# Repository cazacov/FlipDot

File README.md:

# Flip-Dot Displays

Repository structure
## Hardware
Information about flip-dot matrices and controllers.
### Lawo-34 pins
Flip-dot matrices with 34-pins connector having 3 driver chips. For example produced by Lawo.

### Brose-60 pins
Flip-dot matrices with 60-pins connector having 1 driver chip. For example produced by Brose.

### RS-422 Brose VM_IIC

Matrix controller with RS-422 interface

---
All trademarks, logos and brand names are the property of their respective owners. All company, product and service names are for identification purposes only. 

It's a hobby project; I am not affiliated with any  company producing flip-dot displays.

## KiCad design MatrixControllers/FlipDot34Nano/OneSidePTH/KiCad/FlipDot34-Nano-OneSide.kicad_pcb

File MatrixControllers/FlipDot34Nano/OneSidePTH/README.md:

### FlipDot34Nano - One Side PTH

Driver board with Arduino Nano and three 74HC595 shift registers opitmized for single-sided PCB that can be milled with 3018 CNC. 3 digital pins are used for controlling shift registers, analog pins A4 and A5 can be used to receive commands over I2C. Pins A0-A2 connected to DIP switches choosing I2C address.

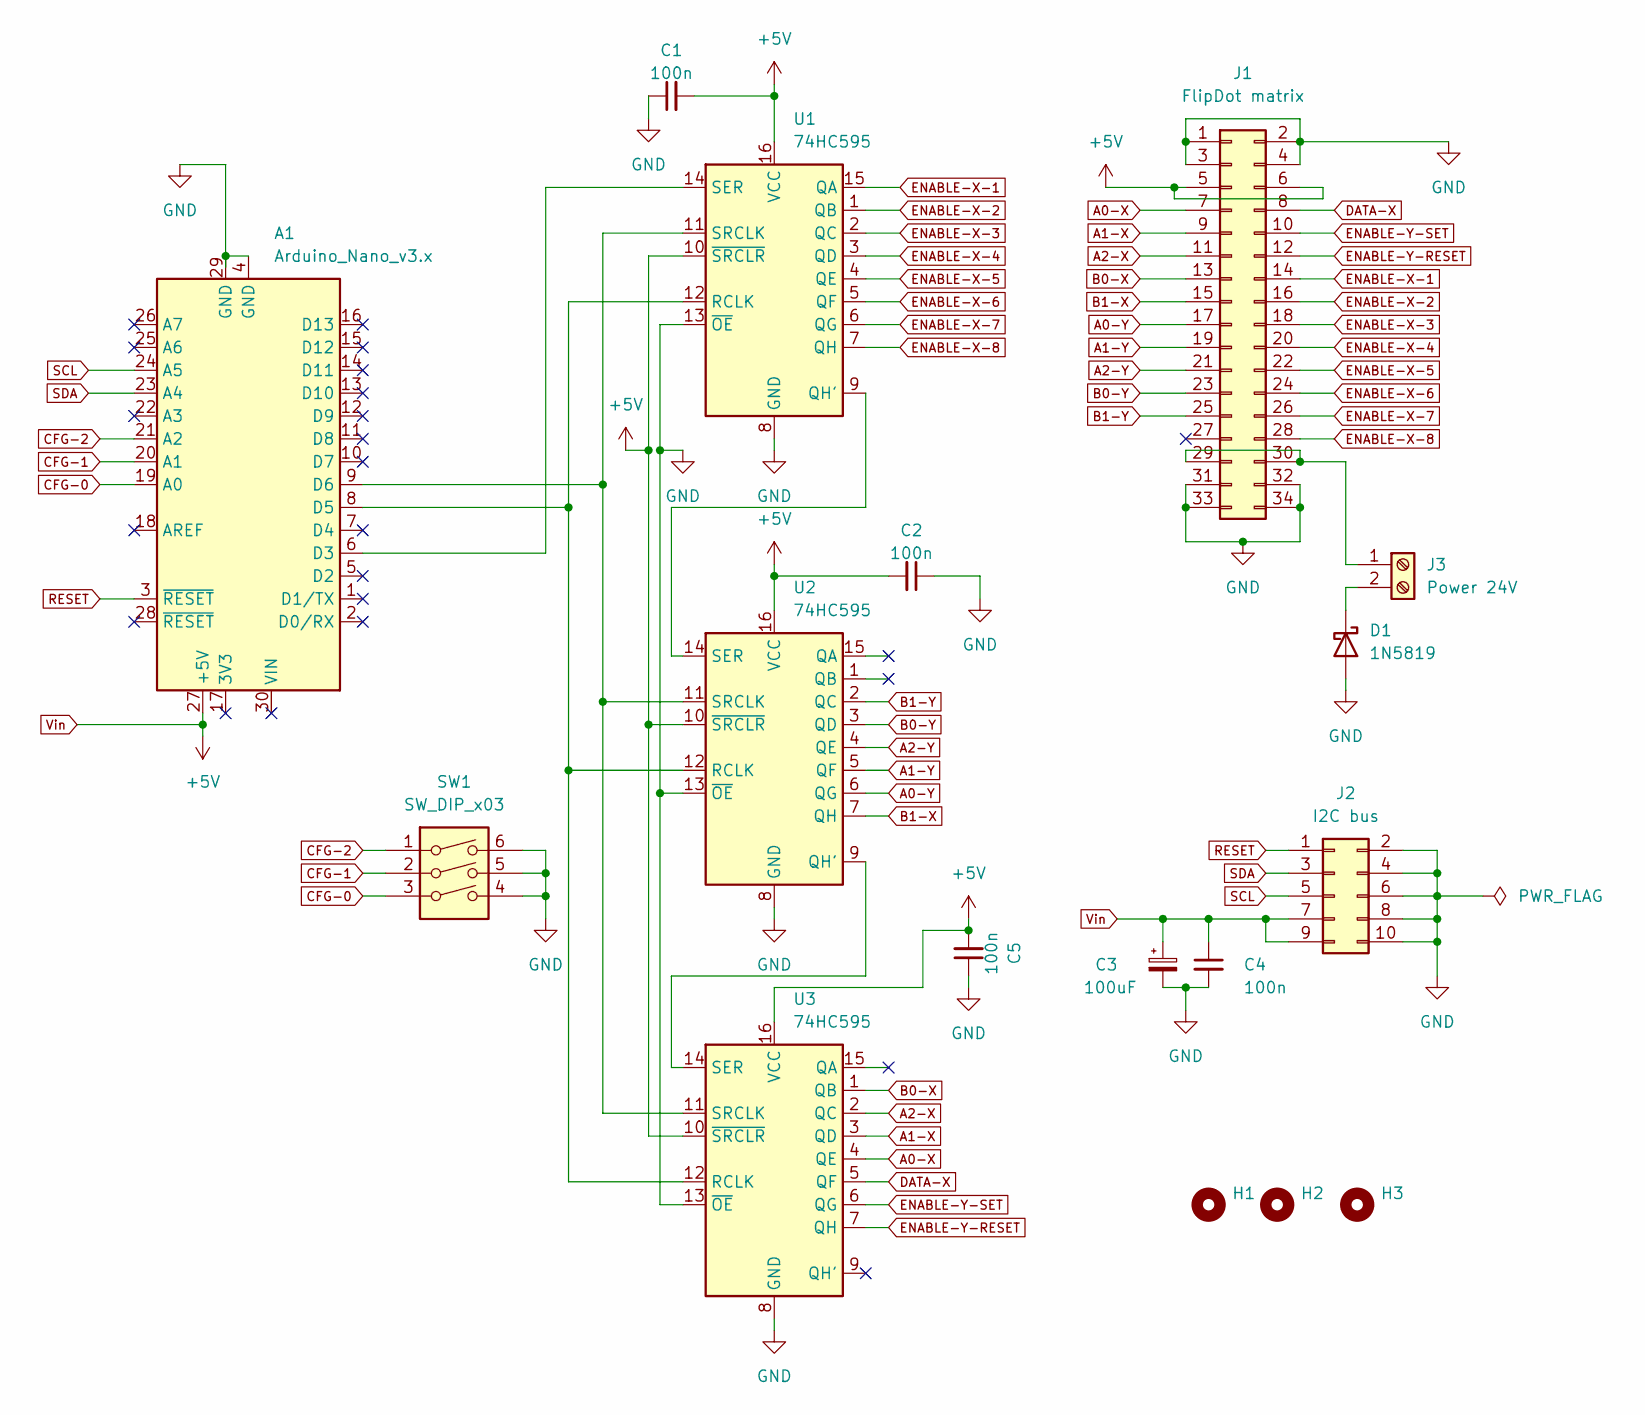
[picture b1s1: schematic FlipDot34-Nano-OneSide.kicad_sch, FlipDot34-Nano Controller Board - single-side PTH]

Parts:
A1: Arduino_Nano_v3.x; Arduino_Nano
C1, C2, C4, C5: 100n; C_Disc_D5.0mm_W2.5mm_P5.00mm
C3: 100uF; CP_Radial_D8.0mm_P3.50mm
D1: 1N5819; D_DO-41_SOD81_P10.16mm_Horizontal
H1, H2, H3: MountingHole; MountingHole_3.2mm_M3
J1: FlipDot matrix; IDC-Header_2x17_P2.54mm_Vertical
J2: I2C bus; IDC-Header_2x05_P2.54mm_Vertical
J3: Power 24V; TerminalBlock_bornier-2_P5.08mm
SW1: SW_DIP_x03; SW_DIP_SPSTx03_Slide_9.78x9.8mm_W7.62mm_P2.54mm
U1, U2, U3: 74HC595; DIP-16_W7.62mm_LongPads

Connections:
A0-X: J1.7, U3.4 (QE)
A0-Y: J1.17, U2.6 (QG)
A1-X: J1.9, U3.3 (QD)
A1-Y: J1.19, U2.5 (QF)
A2-X: J1.11, U3.2 (QC)
A2-Y: J1.21, U2.4 (QE)
B0-X: J1.13, U3.1 (QB)
B0-Y: J1.23, U2.3 (QD)
B1-X: J1.15, U2.7 (QH)
B1-Y: J1.25, U2.2 (QC)
CFG-0: A1.19 (A0), SW1.3
CFG-1: A1.20 (A1), SW1.2
CFG-2: A1.21 (A2), SW1.1
DATA-X: J1.8, U3.5 (QF)
ENABLE-X-1: J1.14, U1.15 (QA)
ENABLE-X-2: J1.16, U1.1 (QB)
ENABLE-X-3: J1.18, U1.2 (QC)
ENABLE-X-4: J1.20, U1.3 (QD)
ENABLE-X-5: J1.22, U1.4 (QE)
ENABLE-X-6: J1.24, U1.5 (QF)
ENABLE-X-7: J1.26, U1.6 (QG)
ENABLE-X-8: J1.28, U1.7 (QH)
ENABLE-Y-RESET: J1.12, U3.7 (QH)
ENABLE-Y-SET: J1.10, U3.6 (QG)
GND: A1.4 (GND), A1.29 (GND), C1.1, C2.1, C3.2, C4.2, C5.1, D1.2 (A), J1.1, J1.2, J1.3, J1.4, J1.31, J1.32, J1.33, J1.34, J2.2, J2.4, J2.6, J2.8, J2.10, SW1.4, SW1.5, SW1.6, U1.8 (GND), U1.13 (~OE), U2.8 (GND), U2.13 (~OE), U3.8 (GND), U3.13 (~OE)
unnamed: A1.6 (D3), U1.14 (SER)
unnamed: A1.8 (D5), U1.12 (RCLK), U2.12 (RCLK), U3.12 (RCLK)
unnamed: A1.9 (D6), U1.11 (SRCLK), U2.11 (SRCLK), U3.11 (SRCLK)
unnamed: D1.1 (K), J3.2
unnamed: J1.29, J1.30, J3.1
unnamed: U1.9 (QH'), U2.14 (SER)
unnamed: U2.9 (QH'), U3.14 (SER)
RESET: A1.3 (~RESET), J2.1
SCL: A1.24 (A5), J2.5
SDA: A1.23 (A4), J2.3
Vin: A1.27 (+5V), C1.2, C2.2, C3.1, C4.1, C5.2, J1.5, J1.6, J2.7, J2.9, U1.10 (~SRCLR), U1.16 (VCC), U2.10 (~SRCLR), U2.16 (VCC), U3.10 (~SRCLR), U3.16 (VCC)

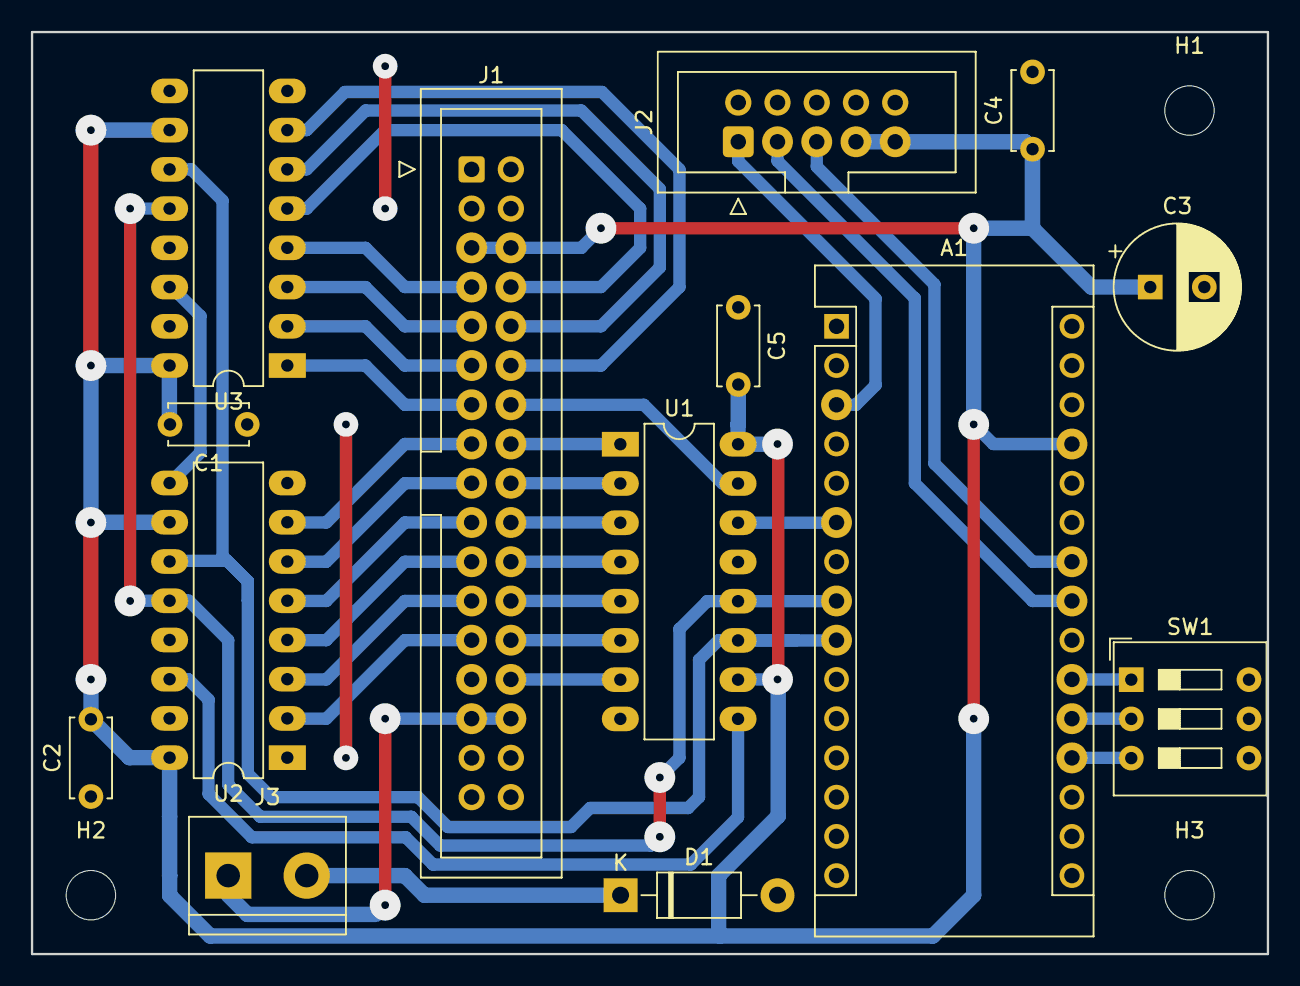
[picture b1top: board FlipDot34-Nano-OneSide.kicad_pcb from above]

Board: 2 copper layers, 80.0 x 59.7 mm, 17 parts (0 on the bottom side), 36 nets.

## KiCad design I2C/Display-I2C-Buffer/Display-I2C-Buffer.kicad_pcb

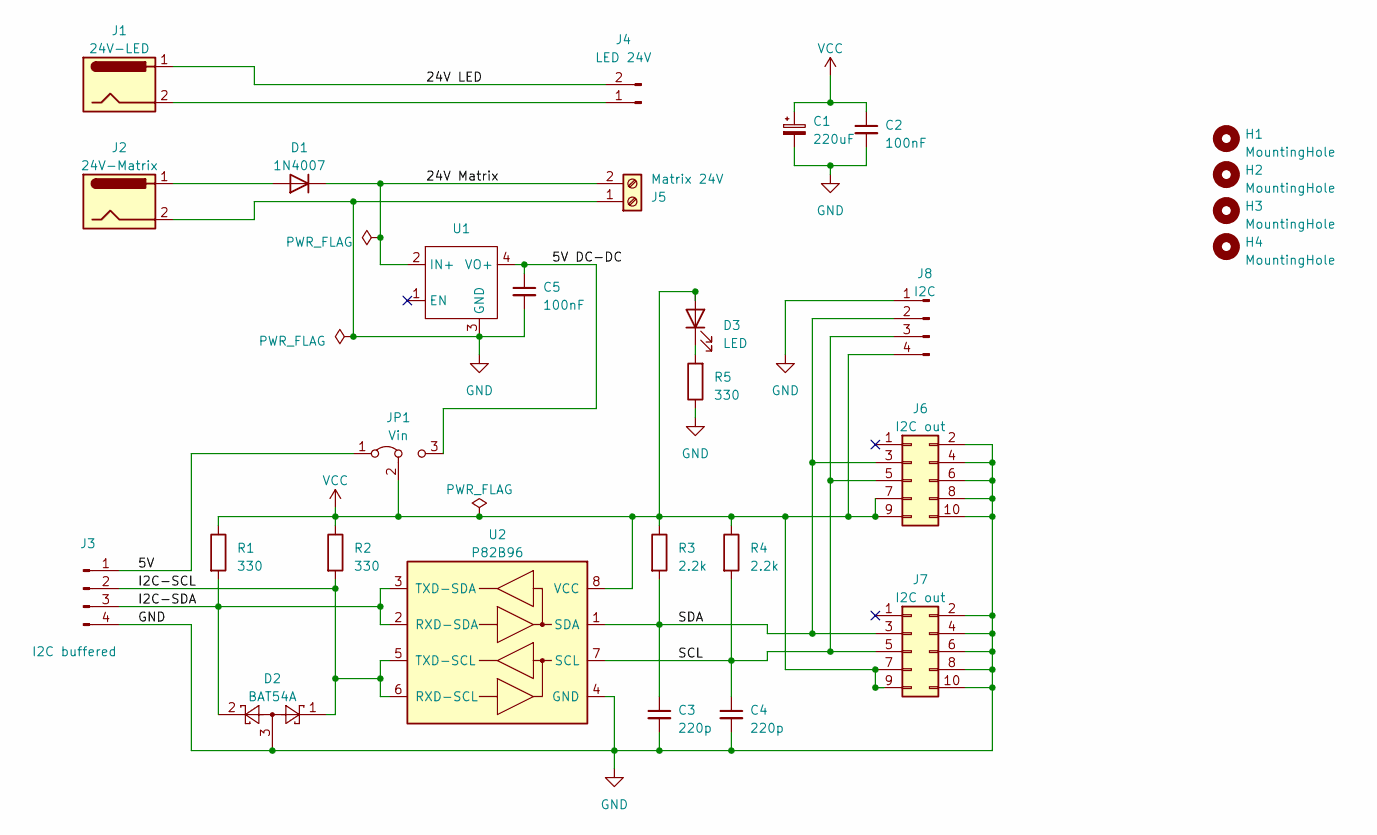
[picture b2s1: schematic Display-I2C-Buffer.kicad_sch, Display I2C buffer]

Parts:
C1: 220uF; CP_Radial_D8.0mm_P3.50mm
C2, C5: 100nF; C_1206_3216Metric
C3, C4: 220p; C_1210_3225Metric_Pad1.33x2.70mm_HandSolder
D1: 1N4007; D_DO-41_SOD81_P10.16mm_Horizontal
D2: BAT54A; SOT-23
D3: LED; LED_0805_2012Metric
H1, H2, H3, H4: MountingHole; MountingHole_3.2mm_M3_DIN965
J1: 24V-LED; BarrelJack_GCT_DCJ200-10-A_Horizontal
J2: 24V-Matrix; BarrelJack_GCT_DCJ200-10-A_Horizontal
J3: I2C buffered; JST_EH_B4B-EH-A_1x04_P2.50mm_Vertical
J4: LED 24V; Molex_KK-396_A-41791-0002_1x02_P3.96mm_Vertical
J5: Matrix 24V; TerminalBlock_bornier-2_P5.08mm
J6, J7: I2C out; IDC-Header_2x05_P2.54mm_Vertical
J8: I2C; PinHeader_1x04_P2.54mm_Vertical
JP1: Vin; PinHeader_1x03_P2.54mm_Vertical
R1, R2, R5: 330; R_1206_3216Metric
R3, R4: 2.2k; R_1206_3216Metric
U1: Mini DC-DC
U2: P82B96; SOIC-8_3.9x4.9mm_P1.27mm

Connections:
/5V: J3.1, JP1.1 (A)
/5V DC-DC: C5.1, JP1.3 (B), U1.4 (VO+)
/24V LED: J1.1, J4.2
/24V Matrix: D1.1 (K), J5.2, U1.2 (IN+)
/I2C-SCL: D2.1, J3.2, R2.2, U2.5 (TXD-SCL), U2.6 (RXD-SCL)
/I2C-SDA: D2.2, J3.3, R1.2, U2.2 (RXD-SDA), U2.3 (TXD-SDA)
/SCL: C4.1, J6.5, J7.5, J8.3, R4.2, U2.7 (SCL)
/SDA: C3.1, J6.3, J7.3, J8.2, R3.2, U2.1 (SDA)
GND: C1.2, C2.2, C3.2, C4.2, C5.2, D2.3, J2.2, J3.4, J5.1, J6.2, J6.4, J6.6, J6.8, J6.10, J7.2, J7.4, J7.6, J7.8, J7.10, J8.1, R5.1, U1.3 (GND), U2.4 (GND)
unnamed: D1.2 (A), J2.1
unnamed: D3.1 (K), R5.2
unnamed: J1.2, J4.1
VCC: C1.1, C2.1, D3.2 (A), J6.7, J6.9, J7.7, J7.9, J8.4, JP1.2 (C), R1.1, R2.1, R3.1, R4.1, U2.8 (VCC)

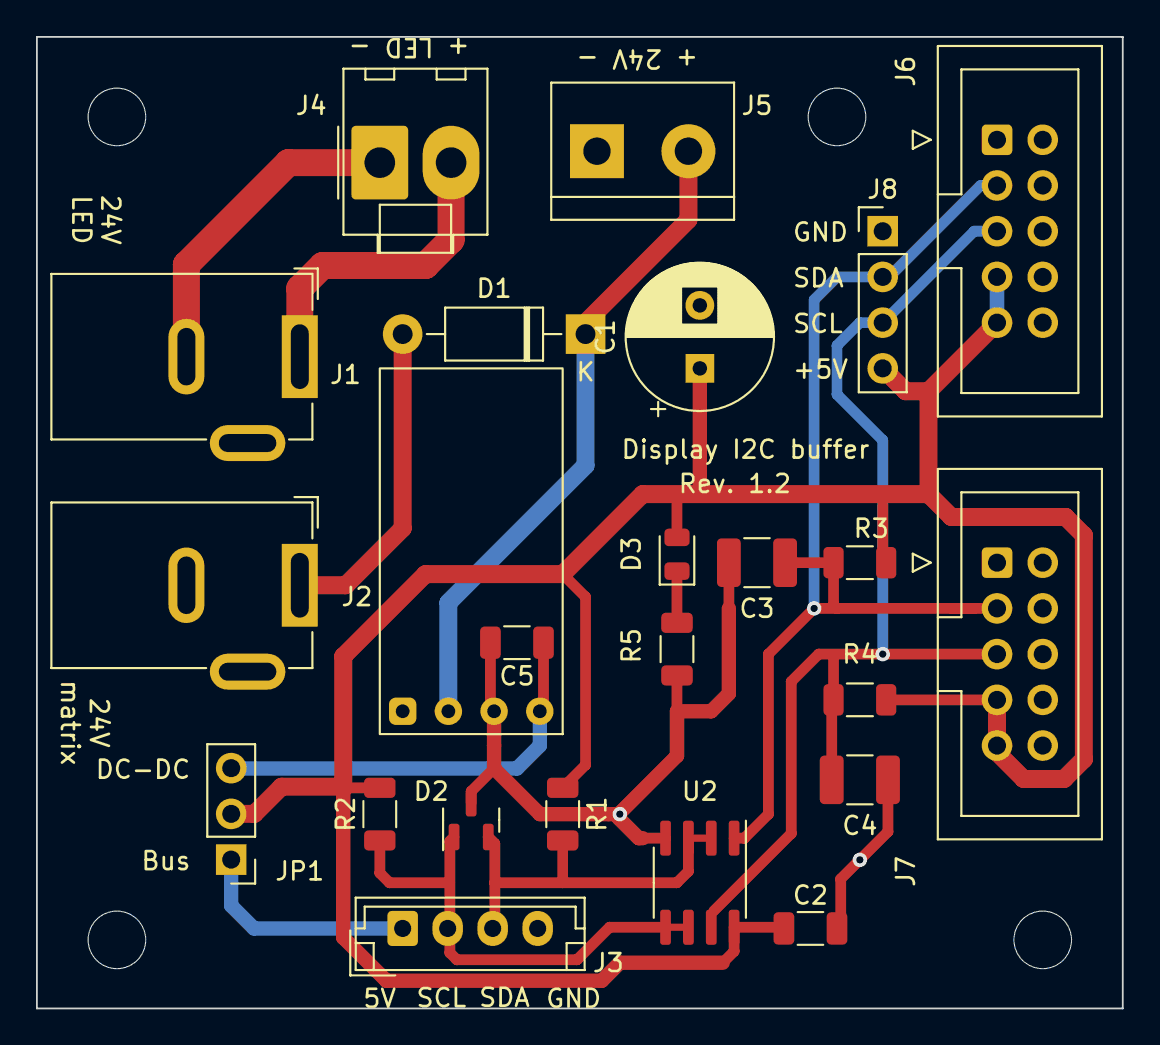
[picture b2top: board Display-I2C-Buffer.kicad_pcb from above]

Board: 2 copper layers, 60.3 x 54.0 mm, 28 parts (0 on the bottom side), 13 nets.

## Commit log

2017-07-30 Show simple bitmap
2017-07-30 Add photo
2017-07-30 Performance test
2018-01-11 Clock test
2018-01-28 Esp8266 as master
2018-02-25 Refactoring
2018-02-25 Add GLCD-font
2018-02-25 Font 14px narrow bold
2018-02-25 Font 12px narrow bold
2018-02-25 Show day of week
2018-02-25 Update dots only when minute changes
2018-02-27 Get Weather data
2018-02-27 Show current temperature
2018-02-27 Show weather icon
2018-03-03 Remove debug prints
2018-03-03 Add russian days of week and months
2018-03-03 Switch off flipboard chip between screen refreshes
2018-03-03 Send Nanos in sleep mode for 48 seconds
2019-12-01 Refactoring: Extract RTC code in separate class
2019-12-20 Trying to port the solution of AdventOfCode Day 13
2019-12-21 Day 13 challenge solved!
2020-11-28 Re-organize code
2020-11-28 Understanding Lawo controller board
2020-11-28 Experiments with wwFlipBoard
2020-11-28 Leo's version
2020-11-28 Fix bug with frame buffer width calculation
2020-11-29 Documentation
2020-11-29 Document I2C bus expansion
2020-12-03 resend ENABLE signal if column driver changed state
2020-12-07 Add KiCad schematics project
2020-12-26 Experiments with SN74LS07N buffer
2020-12-27 Control Brose displays
2020-12-29 Re-structure sources
2020-12-30 Refactor panel code
2020-12-31 Support Adafruit GFX
2021-01-01 Improve buffering
2021-01-01 Nyan cat demo
2021-01-03 Improve stability of the VM_IIC library
2021-01-21 3D model for the case
2021-01-28 Sync and async web servers
2021-01-30 Implement GET data
2021-02-03 Implement POST data method
2021-04-18 Add POST textSmall and textBig handlers
2021-04-18 Clock example
2021-05-02 Case model
2021-05-16 Create React app
2021-05-16 Cleanup
2021-06-22 Firmware decoder project
2021-06-23 Another ROM dump
2021-06-23 Simple rendering
2021-06-24 Add fonts
2021-06-24 Enable high DPI awareness
2021-06-24 Fix auto scrolling
2021-06-24 Improve performance
2021-06-26 Add word length parameter
2021-06-26 Magnification up to 8x8
2021-06-27 Show dump
2021-06-27 Add selection highlighting
2021-06-30 Export font in Adafruit GFX format
2021-07-04 Fonts exporter
2021-07-05 Generate font previews
2021-07-06 Refactoring: show character size in preview
2021-07-06 Export fonts in Adafruit GFX format
2021-07-07 Render placeholders for missing characters
2021-07-07 Bugfix dX value
2021-07-11 Export fonts
2021-07-18 Change matrix size to 140x19
2021-07-18 Use bus fonts
2021-07-18 Fix horizontal spacing
2021-07-18 Minor UI improvements
2021-07-21 Add Game of Life automaton
2021-08-01 Add Test and CLS handlers
2021-08-02 Add Gosper's glider gun
2021-08-09 Support German characters
2021-08-10 Add capital Russian letters
2021-08-11 More characters
2021-08-15 Add bus mode
2021-08-23 Reafactoring
2021-08-23 Add pacman clear screen
2021-08-27 Add counter animation
2021-12-12 Let it snow!
2021-12-12 Better snowflake form
2022-02-27 Snake runner
2022-02-27 Bump follow-redirects from 1.14.1 to 1.14.9 in /webBoard/frontend-react
    Bumps [follow-redirects](https://github.com/follow-redirects/follow-redirects) from 1.14.1 to 1.14.9.
    - [Release notes](https://github.com/follow-redirects/follow-redirects/releases)
    - [Commits](https://github.com/follow-redirects/follow-redirects/compare/v1.14.1...v1.14.9)
    ---
    updated-dependencies:
    - dependency-name: follow-redirects
2022-02-27 Bump url-parse from 1.5.1 to 1.5.10 in /webBoard/frontend-react
    Bumps [url-parse](https://github.com/unshiftio/url-parse) from 1.5.1 to 1.5.10.
    - [Release notes](https://github.com/unshiftio/url-parse/releases)
    - [Commits](https://github.com/unshiftio/url-parse/compare/1.5.1...1.5.10)
    ---
    updated-dependencies:
    - dependency-name: url-parse
2022-02-27 Bump nanoid from 3.1.23 to 3.3.1 in /webBoard/frontend-react
    Bumps [nanoid](https://github.com/ai/nanoid) from 3.1.23 to 3.3.1.
    - [Release notes](https://github.com/ai/nanoid/releases)
    - [Changelog](https://github.com/ai/nanoid/blob/main/CHANGELOG.md)
    - [Commits](https://github.com/ai/nanoid/compare/3.1.23...3.3.1)
    ---
    updated-dependencies:
2022-03-01 Improve gameplay
2022-03-04 Implement A* search
2022-03-04 Fix bugs
2022-03-05 Show planned Path
2022-03-06 Implement FlipDotRenderer
2022-03-06 Update libraries
2022-03-12 Show snake and path with box-drawing symbols
2022-03-13 Alternative flip-dot renderer
2022-03-13 Center on the screen
2022-03-15 Add dataBlock function to the API
2022-03-15 Add title photo
2022-03-15 Add setblock function
2022-03-16 Show score
2022-03-19 Start working on frontend with vue-vite
2022-04-02 Bump minimist from 1.2.5 to 1.2.6 in /webBoard/frontend-vite
    Bumps [minimist](https://github.com/substack/minimist) from 1.2.5 to 1.2.6.
    - [Release notes](https://github.com/substack/minimist/releases)
    - [Commits](https://github.com/substack/minimist/compare/1.2.5...1.2.6)
    ---
    updated-dependencies:
    - dependency-name: minimist
2022-04-05 Support multiple renderers
2022-05-16 Bump async from 2.6.3 to 2.6.4 in /webBoard/frontend-react
    Bumps [async](https://github.com/caolan/async) from 2.6.3 to 2.6.4.
    - [Release notes](https://github.com/caolan/async/releases)
    - [Changelog](https://github.com/caolan/async/blob/v2.6.4/CHANGELOG.md)
    - [Commits](https://github.com/caolan/async/compare/v2.6.3...v2.6.4)
    ---
    updated-dependencies:
2022-05-16 Bump minimist from 1.2.5 to 1.2.6 in /webBoard/frontend-react
    Bumps [minimist](https://github.com/substack/minimist) from 1.2.5 to 1.2.6.
    - [Release notes](https://github.com/substack/minimist/releases)
    - [Commits](https://github.com/substack/minimist/compare/1.2.5...1.2.6)
    ---
    updated-dependencies:
    - dependency-name: minimist
2022-07-20 Bump terser from 5.12.1 to 5.14.2 in /webBoard/frontend-vite
    Bumps [terser](https://github.com/terser/terser) from 5.12.1 to 5.14.2.
    - [Release notes](https://github.com/terser/terser/releases)
    - [Changelog](https://github.com/terser/terser/blob/master/CHANGELOG.md)
    - [Commits](https://github.com/terser/terser/commits)
    ---
    updated-dependencies:
2022-08-30 Bump vite from 1.0.0-rc.13 to 2.9.13 in /webBoard/frontend-vite
    Bumps [vite](https://github.com/vitejs/vite/tree/HEAD/packages/vite) from 1.0.0-rc.13 to 2.9.13.
    - [Release notes](https://github.com/vitejs/vite/releases)
    - [Changelog](https://github.com/vitejs/vite/blob/main/packages/vite/CHANGELOG.md)
    - [Commits](https://github.com/vitejs/vite/commits/v2.9.13/packages/vite)
    ---
    updated-dependencies:
2022-08-30 Bump vite from 2.8.6 to 2.9.13 in /webBoard/frontend-vue
    Bumps [vite](https://github.com/vitejs/vite/tree/HEAD/packages/vite) from 2.8.6 to 2.9.13.
    - [Release notes](https://github.com/vitejs/vite/releases)
    - [Changelog](https://github.com/vitejs/vite/blob/main/packages/vite/CHANGELOG.md)
    - [Commits](https://github.com/vitejs/vite/commits/v2.9.13/packages/vite)
    ---
    updated-dependencies:
2022-11-07 WebBoard simulator
2023-01-08 Implement /data command
2023-01-08 Bump json5 from 1.0.1 to 1.0.2 in /webBoard/frontend-react
    Bumps [json5](https://github.com/json5/json5) from 1.0.1 to 1.0.2.
    - [Release notes](https://github.com/json5/json5/releases)
    - [Changelog](https://github.com/json5/json5/blob/main/CHANGELOG.md)
    - [Commits](https://github.com/json5/json5/compare/v1.0.1...v1.0.2)
    ---
    updated-dependencies:
2023-01-08 Bump qs from 6.5.2 to 6.5.3 in /webBoard/frontend-react
    Bumps [qs](https://github.com/ljharb/qs) from 6.5.2 to 6.5.3.
    - [Release notes](https://github.com/ljharb/qs/releases)
    - [Changelog](https://github.com/ljharb/qs/blob/main/CHANGELOG.md)
    - [Commits](https://github.com/ljharb/qs/compare/v6.5.2...v6.5.3)
    ---
    updated-dependencies:
2023-01-08 Bump decode-uri-component in /webBoard/frontend-react
    Bumps [decode-uri-component](https://github.com/SamVerschueren/decode-uri-component) from 0.2.0 to 0.2.2.
    - [Release notes](https://github.com/SamVerschueren/decode-uri-component/releases)
    - [Commits](https://github.com/SamVerschueren/decode-uri-component/compare/v0.2.0...v0.2.2)
    ---
    updated-dependencies:
    - dependency-name: decode-uri-component
2023-01-08 Bump express from 4.17.1 to 4.18.2 in /webBoard/frontend-react
    Bumps [express](https://github.com/expressjs/express) from 4.17.1 to 4.18.2.
    - [Release notes](https://github.com/expressjs/express/releases)
    - [Changelog](https://github.com/expressjs/express/blob/master/History.md)
    - [Commits](https://github.com/expressjs/express/compare/4.17.1...4.18.2)
    ---
    updated-dependencies:
2023-01-08 Bump loader-utils and react-scripts in /webBoard/frontend-react
    Bumps [loader-utils](https://github.com/webpack/loader-utils) to 2.0.4 and updates ancestor dependency [react-scripts](https://github.com/facebook/create-react-app/tree/HEAD/packages/react-scripts). 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
    Updates `loader-utils` from 1.2.3 to 2.0.4
    - [Release notes](https://github.com/webpack/loader-utils/releases)
    - [Changelog](https://github.com/webpack/loader-utils/blob/v2.0.4/CHANGELOG.md)
    - [Commits](https://github.com/webpack/loader-utils/compare/v1.2.3...v2.0.4)
    Updates `react-scripts` from 4.0.3 to 5.0.1
2023-01-09 Support more commands
2023-01-10 Dino runner
2023-01-10 Bump debug and react-scripts in /webBoard/frontend-react
    Bumps [debug](https://github.com/debug-js/debug) to 4.3.4 and updates ancestor dependency [react-scripts](https://github.com/facebook/create-react-app/tree/HEAD/packages/react-scripts). These depende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
    Updates `debug` from 2.6.9 to 4.3.4
    - [Release notes](https://github.com/debug-js/debug/releases)
    - [Commits](https://github.com/debug-js/debug/compare/2.6.9...4.3.4)
    Updates `react-scripts` from 4.0.3 to 5.0.1
    - [Release notes](https://github.com/facebook/create-react-app/releases)
2023-01-11 Implement jumps
2023-03-07 Bump minimist from 1.2.5 to 1.2.8 in /webBoard/frontend-vite
    Bumps [minimist](https://github.com/minimistjs/minimist) from 1.2.5 to 1.2.8.
    - [Release notes](https://github.com/minimistjs/minimist/releases)
    - [Changelog](https://github.com/minimistjs/minimist/blob/main/CHANGELOG.md)
    - [Commits](https://github.com/minimistjs/minimist/compare/v1.2.5...v1.2.8)
    ---
    updated-dependencies:
2023-04-12 Improve snake game
2023-04-12 re-organize folders
2023-04-16 Design case
2023-07-30 Add I2C header
2023-09-04 Brose RS-485 version
2023-11-02 Add Waiting animation
2024-03-15 Add Hardware -> Lawo pinout and images
2024-03-15 Add KiCad project - FlipDot34Nano single side PTH version
2024-03-15 Add VM_IIC board
2024-03-16 Document VM_IIC board
2024-05-05 Display host with RS485 interface
